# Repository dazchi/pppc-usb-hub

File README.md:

# Per-port Power Control USB HUB

## Key Features
* 3-port USB hub fully compatiable with USB High-Speed(480Hz), Full-Speed(12Hz) and Low-Speed(1.5MHz) devices
* Supports per-port power control, current limitation and thermal shutdown protection
* No special driver required, reuses the driver from the widely known CH340 USB-to-serial chip
* Supports 5V 2A external USB-C power supply
* Reverse current protection along with resetable fuse
* Relay: SRD-05VDC-SL-C 10A 30VDC, 10A 250VAC
* Customized settings stored in built-in flash memory

## Schematic & Layout (Designed w/ KiCAD 8.0)

## 3D Printed Case (Designed w/ Fusion 360)

## Basic Control Commands (Group Control)
Turn On:  ```A0 01 01 A2```
  
Turn Off: ```A0 01 00 A1```
  
*These commands are designed to mimic the command of **[USB RELAY](https://www.smart-prototyping.com/USB-Relay-1-Channel)** on purpose*  

## Advanced Control Commands

### Per-port control
Foramt: ```F0 {AA} {BB} {ZZ} ```  

* ```{AA}``` Port Address:  
  | Port | Address |
  |:----:|:-------:|
  | USB1 |   0x01  |
  | USB2 |   0x02  |
  | USB3 |   0x03  |
  | Relay|   0x04  |

*  ```{BB}``` On/Off:  
    * ON: ```0x01```  
    * OFF: ```0x00```  

* ```{ZZ}``` Checksum:  
 ```ZZ = (0xF0 + {AA} + {BB}) & 0xFF```

Example:  
* Turn on USB1: ```F0 01 01 F2```  
* Turn off Relay: ```F0 04 00 F4```  

### Write Device Settings
Format:  
* Command: ```AB CD EF 67 {X1 X2 X3 X4} ZZ```:

    *  ```{X1 X2 X3 X4}``` Device Settings:  
        |          |                       |
        |:--------:|:---------------------:|
        | ```X1``` |   USB1 Port Settings  |
        | ```X2``` |   USB2 Port Settings  |
        | ```X3``` |   USB3 Port Settings  |
        | ```X4``` |  Relay Port Settings  |
        ```c
        typedef struct DeviceSettings
        {
            PortSettings_t usb1;
            PortSettings_t usb2;
            PortSettings_t usb3;
            PortSettings_t relay;
        } __attribute__((packed)) DeviceSettings_t;
        ```
        * Port Settings:  
            |  Bit Field |  Setting  |  Description |
            |:--------:|:---------------------:|:------------------|
            | b0 |   Port Default State  | Default state of port while power on  |
            | b1 |   *Group Control       | 0: Disable group control (ignores **Basic Control Commands**)<br>1: Enable group control
            | b2 |   *Polarity  | Polarity of the port during group control<br>0: Default polarity<br>1: Reversed polarity
            | b3 ~ b7 |  Reserved  |  Reserved for future use   |

            **The **Group Control** and the **Polarity** only affets the **Basic Control Commands***
            ```c
            typedef struct PortSettings
            {
                uint8_t defaultState :1;
                uint8_t groupControl :1;
                uint8_t polarity :1;
                uint8_t reserved :5;
            } __attribute__((packed)) PortSettings_t;
            ```
    * ```{ZZ}``` Checksum:  
    ```ZZ = (0xAB + 0xCD + 0xEF + 0x67 + {X1} {X2} {X3} {X4}) & 0xFF```

* Response:  
    ```SUCCESS``` or ```FAILED```

Example:  
* Defaut Devcie Settings  
    TX: ```AB CD EF 67 07 07 07 02 E5```  
    RX: ```SUCCESS```  

    This command sets the default state of USB1, USB2 and USB3 to On, the default state of Relay to Off.  
    The "Turn on" command ```A0 01 01 A2``` turns on the relay but turns off USB1, USB2 and USB3.  
    The "Turn off" command ```A0 01 00 A1``` turns off the relay but turns on USB1, USB2 and USB3.

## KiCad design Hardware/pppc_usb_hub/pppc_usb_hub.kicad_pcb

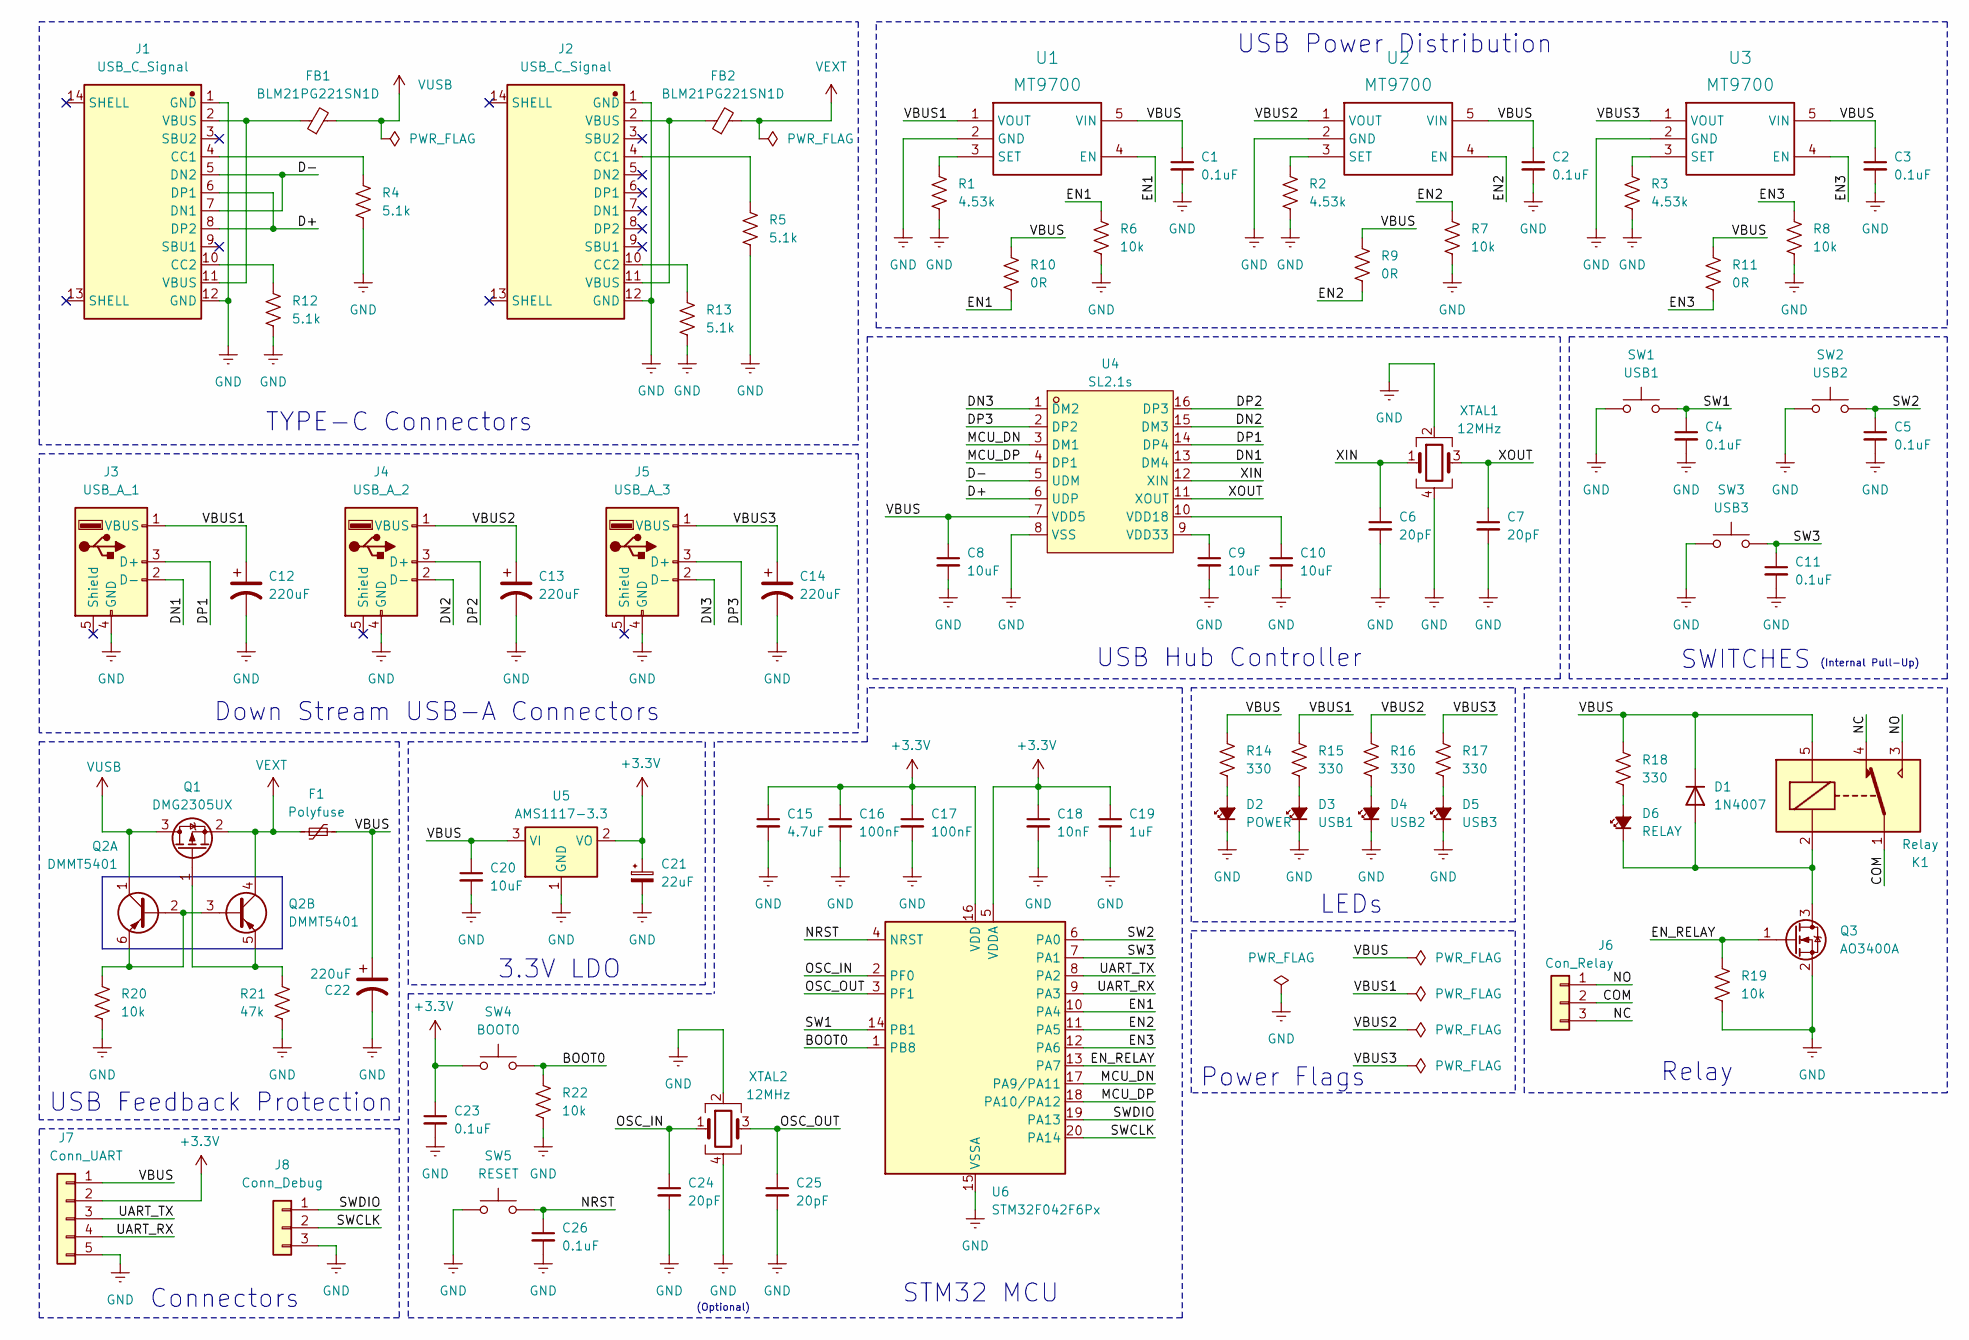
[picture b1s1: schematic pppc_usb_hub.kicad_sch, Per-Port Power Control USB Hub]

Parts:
C1, C2, C3, C4, C5, C11, C23, C26: 0.1uF; C_0603_1608Metric
C6, C7, C24, C25: 20pF; C_0603_1608Metric
C8, C9, C10, C20: 10uF; C_0603_1608Metric
C12, C13, C14, C22: 220uF; CP_Elec_6.3x7.7
C15: 4.7uF; C_0603_1608Metric
C16, C17: 100nF; C_0603_1608Metric
C18: 10nF; C_0603_1608Metric
C19: 1uF; C_0603_1608Metric
C21: 22uF; CP_EIA-3216-10_Kemet-I
D1: 1N4007; D_SOD-123F
D2: POWER; LED_0603_1608Metric
D3: USB1; LED_0603_1608Metric
D4: USB2; LED_0603_1608Metric
D5: USB3; LED_0603_1608Metric
D6: RELAY; LED_0603_1608Metric
F1: Polyfuse; C_0805_2012Metric
FB1, FB2: BLM21PG221SN1D; Fuse_0805_2012Metric
J1, J2: USB_C_Signal; USB-C-SMD_TYPE-C-6PIN-2MD-073
J3: USB_A_1; USB-A-TH_AF-10.0-HC6.3
J4: USB_A_2; USB-A-TH_USB-M-22
J5: USB_A_3; USB-A-TH_USB-M-22
J6: Con_Relay; CONN-TH_3P-P5.08_DB128L-5.08-3P-OG-S
J7: Conn_UART; PinHeader_1x05_P2.54mm_Vertical
J8: Conn_Debug; PinHeader_1x03_P2.54mm_Vertical
K1: Relay; Relay_SPDT_SANYOU_SRD_Series_Form_C
Q1: DMG2305UX; SOT-23
Q2: DMMT5401; SOT-23-6
Q3: AO3400A; SOT-23
R1, R2, R3: 4.53k; R_0603_1608Metric
R4, R5, R12, R13: 5.1k; R_0603_1608Metric
R6, R7, R8, R19, R20, R22: 10k; R_0603_1608Metric
R9, R10, R11: 0R; R_0603_1608Metric
R14, R15, R16, R17, R18: 330; R_0603_1608Metric
R21: 47k; R_0603_1608Metric
SW1: USB1; SW-SMD_GT-TC020B-H035-L05
SW2: USB2; SW-SMD_GT-TC020B-H035-L05
SW3: USB3; SW-SMD_GT-TC020B-H035-L05
SW4: BOOT0; SW-SMD_GT-TC020B-H035-L05
SW5: RESET; SW-SMD_L6.0-W3.3-LS8.0
U1, U2, U3: MT9700; SOT-23-5_L3.0-W1.7-P0.95-LS2.8-BR
U4: SL2.1s; SSOP-16_L4.6-W2.6-P0.53-LS4.0-BL
U5: AMS1117-3.3; SOT-223-3_TabPin2
U6: STM32F042F6Px; TSSOP-20_4.4x6.5mm_P0.65mm
XTAL1, XTAL2: 12MHz; OSC-SMD_4P-L3.2-W2.5-BL

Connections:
+3.3V: C15.1, C16.1, C17.1, C18.1, C19.1, C21.1, C23.1, J7.2, SW4.2, U5.2 (VO), U6.5 (VDDA), U6.16 (VDD)
/BOOT0: R22.1, SW4.1, U6.1 (PB8)
/COM: J6.2, K1.1
/D+: J1.6 (DP1), J1.8 (DP2), U4.6 (UDP)
/D-: J1.5 (DN2), J1.7 (DN1), U4.5 (UDM)
/DN1: J3.2 (D-), U4.13 (DM4)
/DN2: J4.2 (D-), U4.15 (DM3)
/DN3: J5.2 (D-), U4.1 (DM2)
/DP1: J3.3 (D+), U4.14 (DP4)
/DP2: J4.3 (D+), U4.16 (DP3)
/DP3: J5.3 (D+), U4.2 (DP2)
/EN1: R6.1, R10.2, U1.4 (EN), U6.10 (PA4)
/EN2: R7.1, R9.2, U2.4 (EN), U6.11 (PA5)
/EN3: R8.1, R11.2, U3.4 (EN), U6.12 (PA6)
/EN_RELAY: Q3.1 (G), R19.1, U6.13 (PA7)
/MCU_DN: U4.3 (DM1), U6.17 (PA9/PA11)
/MCU_DP: U4.4 (DP1), U6.18 (PA10/PA12)
/NC: J6.3, K1.4
/NO: J6.1, K1.3
/NRST: C26.1, SW5.1, U6.4 (NRST)
/OSC_IN: C24.1, U6.2 (PF0), XTAL2.1
/OSC_OUT: C25.1, U6.3 (PF1), XTAL2.3
/SW1: C4.1, SW1.1, U6.14 (PB1)
/SW2: C5.1, SW2.1, U6.6 (PA0)
/SW3: C11.1, SW3.1, U6.7 (PA1)
/SWCLK: J8.2, U6.20 (PA14)
/SWDIO: J8.1, U6.19 (PA13)
/UART_RX: J7.4, U6.9 (PA3)
/UART_TX: J7.3, U6.8 (PA2)
/VBUS: C1.1, C2.1, C3.1, C8.1, C20.1, C22.1, D1.1 (K), F1.2, J7.1, K1.5, R9.1, R10.1, R11.1, R14.1, R18.1, U1.5 (VIN), U2.5 (VIN), U3.5 (VIN), U4.7 (VDD5), U5.3 (VI)
/VBUS1: C12.1, J3.1 (VBUS), R15.1, U1.1 (VOUT)
/VBUS2: C13.1, J4.1 (VBUS), R16.1, U2.1 (VOUT)
/VBUS3: C14.1, J5.1 (VBUS), R17.1, U3.1 (VOUT)
/XIN: C6.1, U4.12 (XIN), XTAL1.1
/XOUT: C7.1, U4.11 (XOUT), XTAL1.3
GND: C1.2, C2.2, C3.2, C4.2, C5.2, C6.2, C7.2, C8.2, C9.2, C10.2, C11.2, C12.2, C13.2, C14.2, C15.2, C16.2, C17.2, C18.2, C19.2, C20.2, C21.2, C22.2, C23.2, C24.2, C25.2, C26.2, D2.1 (K), D3.1 (K), D4.1 (K), D5.1 (K), J1.1 (GND), J1.12 (GND), J2.1 (GND), J2.12 (GND), J3.4 (GND), J4.4 (GND), J5.4 (GND), J7.5, J8.3, Q3.2 (S), R1.2, R2.2, R3.2, R4.2, R5.2, R6.2, R7.2, R8.2, R12.2, R13.2, R19.2, R20.2, R21.2, R22.2, SW1.2, SW2.2, SW3.2, SW5.2, U1.2 (GND), U2.2 (GND), U3.2 (GND), U4.8 (VSS), U5.1 (GND), U6.15 (VSSA), XTAL1.2, XTAL1.4, XTAL2.2, XTAL2.4
unnamed: D1.2 (A), D6.1 (K), K1.2, Q3.3 (D)
unnamed: D2.2 (A), R14.2
unnamed: D3.2 (A), R15.2
unnamed: D4.2 (A), R16.2
unnamed: D5.2 (A), R17.2
unnamed: D6.2 (A), R18.2
unnamed: FB1.1, J1.2 (VBUS), J1.11 (VBUS)
unnamed: FB2.1, J2.2 (VBUS), J2.11 (VBUS)
unnamed: J1.4 (CC1), R4.1
unnamed: J1.10 (CC2), R12.1
unnamed: J2.4 (CC1), R5.1
unnamed: J2.10 (CC2), R13.1
unnamed: Q1.1 (G), Q2.5 (E2), R21.1
unnamed: Q2.2 (B1), Q2.3 (B2), Q2.6 (E1), R20.1
unnamed: R1.1, U1.3 (SET)
unnamed: R2.1, U2.3 (SET)
unnamed: R3.1, U3.3 (SET)
unnamed: C10.1, U4.10 (VDD18)
unnamed: C9.1, U4.9 (VDD33)
VEXT: F1.1, FB2.2, Q1.2 (S), Q2.4 (C2)
VUSB: FB1.2, Q1.3 (D), Q2.1 (C1)

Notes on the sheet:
3.3V LDO
Relay
Connectors
(Internal Pull-Up)
Power Flags
(Optional)
LEDs
TYPE-C Connectors
STM32 MCU
USB Hub Controller
Down Stream USB-A Connectors
USB Power Distribution
SWITCHES
USB Feedback Protection

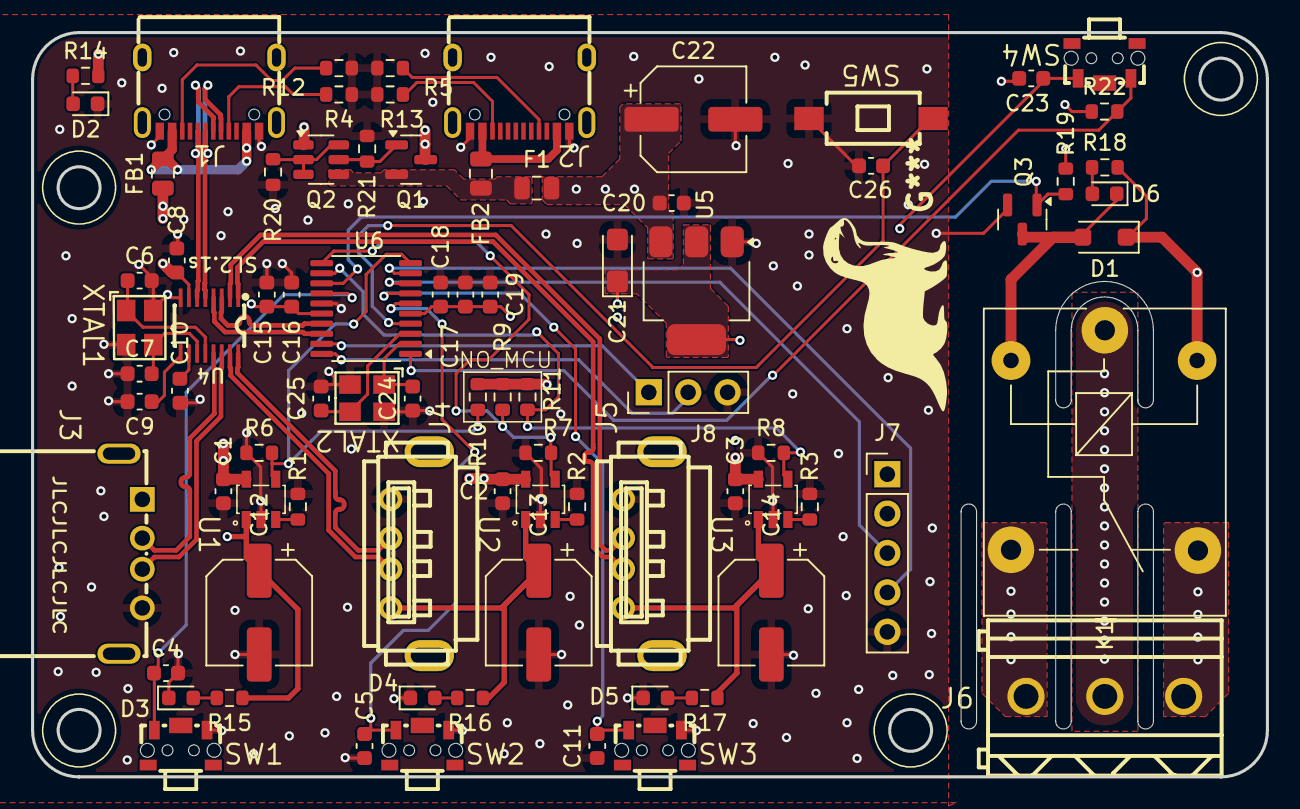
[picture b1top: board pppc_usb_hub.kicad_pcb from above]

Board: 4 copper layers, 79.6 x 48.0 mm, 82 parts (0 on the bottom side), 57 nets.

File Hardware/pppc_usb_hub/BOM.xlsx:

Reference | Value | Datasheet | Footprint | Qty | DNP | MSRP |  | Total
C1,C2,C3,C4,C5,C11,C25 | 0.1uF | https://www.lcsc.com/product-detail/Multilayer-Ceramic-Capac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 | Capacitor_SMD:C_0201_0603Metric | 7 |  | 2.3999999999999998E-3 |  | 3.8712
C6,C7,C23,C24 | 20pF | https://www.lcsc.com/product-detail/Multilayer-Ceramic-Capac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 | Capacitor_SMD:C_0201_0603Metric | 4 |  | 1.4E-2
C8,C9,C10,C20 | 10uF | https://www.lcsc.com/product-detail/Multilayer-Ceramic-Capac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 | Capacitor_SMD:C_0201_0603Metric | 4 |  | 4.4000000000000003E-3
C12,C13,C14,C22 | 220uF | https://www.lcsc.com/product-detail/Solid-Capacitors_Honor-E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 | Capacitor_SMD:CP_Elec_6.3x7.7 | 4 |  | 0.14080000000000001
C15 | 4.7uF | https://www.lcsc.com/product-detail/Multilayer-Ceramic-Capac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 | Capacitor_SMD:C_0201_0603Metric | 1 |  | 4.1000000000000003E-3
C16,C17 | 100nF | https://www.lcsc.com/product-detail/Multilayer-Ceramic-Capac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 | Capacitor_SMD:C_0201_0603Metric | 2 |  | 2.3999999999999998E-3
C18 | 10nF | https://www.lcsc.com/product-detail/Multilayer-Ceramic-Capac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 | Capacitor_SMD:C_0201_0603Metric | 1 |  | 1.9E-3
C19 | 1uF | https://www.lcsc.com/product-detail/Multilayer-Ceramic-Capac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 | Capacitor_SMD:C_0201_0603Metric | 1 |  | 4.1999999999999997E-3
C21 | 22uF | https://www.lcsc.com/product-detail/Tantalum-Capacitors_KEME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 | Capacitor_Tantalum_SMD:CP_EIA-3216-10_Kemet-I | 1 |  | 8.0100000000000005E-2
D1 | 1N4007 | https://www.lcsc.com/product-detail/Diodes-General-Purpose_M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 | Diode_SMD:D_SOD-123F | 1 |  | 3.8E-3
D2 | POWER | https://www.lcsc.com/product-detail/Light-Emitting-Diodes-LE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 | LED_SMD:LED_0201_0603Metric | 1 |  | 5.1000000000000004E-3
D3 | USB1 | https://www.lcsc.com/product-detail/Light-Emitting-Diodes-LE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 | LED_SMD:LED_0201_0603Metric | 1 |  | 5.3E-3
D4 | USB2 | https://www.lcsc.com/product-detail/Light-Emitting-Diodes-LE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 | LED_SMD:LED_0201_0603Metric | 1 |  | 5.3E-3
D5 | USB3 | https://www.lcsc.com/product-detail/Light-Emitting-Diodes-LE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 | LED_SMD:LED_0201_0603Metric | 1 |  | 5.3E-3
D6 | RELAY | https://www.lcsc.com/product-detail/Light-Emitting-Diodes-LE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 | LED_SMD:LED_0201_0603Metric | 1 |  | 5.3E-3
F1 | Polyfuse | https://www.lcsc.com/product-detail/Resettable-Fuses_LUTE-08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 | Capacitor_SMD:C_0805_2012Metric | 1 |  | 5.8400000000000001E-2
FB1,FB2 | BLM21PG221SN1D | https://www.lcsc.com/product-detail/Ferrite-Beads_Murata-Ele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 | Fuse:Fuse_0805_2012Metric | 2 |  | 1.4800000000000001E-2
J1,J2 | USB_C_Signal | https://www.lcsc.com/product-detail/USB-Connectors_SHOU-HAN-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 | PCBLIB_USB-C-SMD_TYPE-C-6PIN-2MD-073_2024-05-18:USB-C-SMD_TYPE-C-6PIN-2MD-073 | 2 |  | 5.0099999999999999E-2
J3 | USB_A_1 | https://www.lcsc.com/product-detail/USB-Connectors_SHOU-HAN-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 | PCBLIB_USB-A-TH_AF-10.0-HC6.3_2024-05-20:USB-A-TH_AF-10.0-HC6.3 | 1 |  | 3.6200000000000003E-2
J4 | USB_A_2 | https://www.lcsc.com/product-detail/USB-Connectors_Ckmtw-She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 | PCBLIB_USB-A-TH_USB-M-22_2024-05-19:USB-A-TH_USB-M-22 | 1 |  | 0.15040000000000001
J5 | USB_A_3 | https://www.lcsc.com/product-detail/USB-Connectors_Ckmtw-She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 | PCBLIB_USB-A-TH_USB-M-22_2024-05-19:USB-A-TH_USB-M-22 | 1 |  | 0.15040000000000001
J6 | Con_Relay | https://www.lcsc.com/product-detail/Screw-terminal_DORABO-DB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 | PCBLIB_CONN-TH_3P-P5.08_DB128L-5.08-3P-OG-S_2024-05-19:CONN-TH_3P-P5.08_DB128L-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 | 1 |  | 0.18010000000000001
J7 | Conn_UART | https://www.lcsc.com/product-detail/Pin-Headers_Hanbo-Electr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 | Connector_PinHeader_2.54mm:PinHeader_1x05_P2.54mm_Vertical | 1 |  | 2.23E-2
J8 | Conn_Debug | ~ | Connector_PinHeader_2.54mm:PinHeader_1x03_P2.54mm_Vertical | 1
K1 | Relay | https://www.lcsc.com/product-detail/Power-Relays_Ningbo-Song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 | Relay_THT:Relay_SPDT_SANYOU_SRD_Series_Form_C | 1 |  | 0.31240000000000001
Q1 | DMG2305UX | https://www.lcsc.com/product-detail/MOSFETs_TECH-PUBLIC-DMG2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 | Package_TO_SOT_SMD:SOT-23 | 1 |  | 5.1700000000000003E-2
Q2 | DMMT5401 | https://www.lcsc.com/product-detail/Bipolar-Transistors-BJT_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 | Package_TO_SOT_SMD:SOT-23-6 | 1 |  | 0.16830000000000001
Q3 | AO3400A | https://www.lcsc.com/product-detail/MOSFETs_UMW-Youtai-Semic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 | Package_TO_SOT_SMD:SOT-23 | 1 |  | 2.7799999999999998E-2
R1,R2,R3 | 4.53k | https://www.lcsc.com/product-detail/Chip-Resistor-Surface-Mo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 | Resistor_SMD:R_0201_0603Metric | 3 |  | 1.1999999999999999E-3
R4,R5,R12,R13 | 5.1k | https://www.lcsc.com/product-detail/Chip-Resistor-Surface-Mo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 | Resistor_SMD:R_0201_0603Metric | 4 |  | 0.0010
R6,R7,R8,R19,R20,R22 | 10k | https://www.lcsc.com/product-detail/Chip-Resistor-Surface-Mo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 | Resistor_SMD:R_0201_0603Metric | 6 |  | 8.9999999999999998E-4
R9,R10,R11 | 0R | ~ | Resistor_SMD:R_0201_0603Metric | 3
R14,R15,R16,R17,R18 | 330 | https://www.lcsc.com/product-detail/Chip-Resistor-Surface-Mo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 | Resistor_SMD:R_0201_0603Metric | 5 |  | 1E-3
R21 | 47k | https://www.lcsc.com/product-detail/Chip-Resistor-Surface-Mo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 | Resistor_SMD:R_0201_0603Metric | 1 |  | 1E-3
SW1 | USB1 | https://www.lcsc.com/product-detail/Tactile-Switches_G-Switc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 | PCBLIB_SW-SMD_GT-TC020B-H035-L05_2024-05-21:SW-SMD_GT-TC020B-H035-L05 | 1 |  | 7.2599999999999998E-2
SW2 | USB2 | https://www.lcsc.com/product-detail/Tactile-Switches_G-Switc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 | PCBLIB_SW-SMD_GT-TC020B-H035-L05_2024-05-21:SW-SMD_GT-TC020B-H035-L05 | 1 |  | 7.2599999999999998E-2
SW3 | USB3 | https://www.lcsc.com/product-detail/Tactile-Switches_G-Switc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 | PCBLIB_SW-SMD_GT-TC020B-H035-L05_2024-05-21:SW-SMD_GT-TC020B-H035-L05 | 1 |  | 7.2599999999999998E-2
SW4 | BOOT0 | https://www.lcsc.com/product-detail/Tactile-Switches_XKB-Con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 | PCBLIB_SW-SMD_L6.0-W3.3-LS8.0_2024-05-19:SW-SMD_L6.0-W3.3-LS8.0 | 1 |  | 0.0323
SW5 | RESET | https://www.lcsc.com/product-detail/Tactile-Switches_XKB-Con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 | PCBLIB_SW-SMD_L6.0-W3.3-LS8.0_2024-05-19:SW-SMD_L6.0-W3.3-LS8.0 | 1 |  | 0.0323
U1,U2,U3 | MT9700 | https://www.lcsc.com/product-detail/span-style-background-co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 | PCBLIB_SOT-23-5_L3.0-W1.7-P0.95-LS2.8-BR_2024-05-18:SOT-23-5_L3.0-W1.7-P0.95-LS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 | 3 |  | 3.56E-2
U4 | SL2.1s | https://www.lcsc.com/product-detail/USB-Converters_CoreChips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 | PCB_NEW_PCB_2024-05-14:SSOP-16_L4.6-W2.6-P0.53-LS4.0-BL | 1 |  | 0.20499999999999999
U5 | AMS1117-3.3 | https://www.lcsc.com/product-detail/Linear-Voltage-Regulator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 | Package_TO_SOT_SMD:SOT-223-3_TabPin2 | 1 |  | 0.1298
U6 | STM32F042F6Px | https://www.lcsc.com/product-detail/Microcontroller-Units-MC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 | Package_SO:TSSOP-20_4.4x6.5mm_P0.65mm | 1 |  | 1.1457999999999999
XTAL1,XTAL2 | 12MHz | https://www.lcsc.com/product-detail/Crystals_YXC-X322512MSB4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 | PCBLIB_OSC-SMD_4P-L3.2-W2.5-BL_2024-05-18:OSC-SMD_4P-L3.2-W2.5-BL | 2 |  | 5.7099999999999998E-2

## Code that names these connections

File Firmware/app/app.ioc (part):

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Mcu.Name=STM32F042F6Px
Mcu.Package=TSSOP20
Mcu.UserName=STM32F042F6Px
PA0.Signal=GPIO_Input
PA1.Signal=GPIO_Input
PA11.Mode=Device
PA11.Signal=USB_DM
PA12.Mode=Device
PA12.Signal=USB_DP
PA13.Mode=Serial_Wire
PA13.Signal=SYS_SWDIO
PA14.Mode=Serial_Wire
PA14.Signal=SYS_SWCLK
PA2.Mode=Asynchronous
PA2.Signal=USART2_TX
PA3.Mode=Asynchronous
PA3.Signal=USART2_RX
PA4.Signal=GPIO_Output
PA5.Signal=GPIO_Output
PA6.Signal=GPIO_Output
PA7.Signal=GPIO_Output
PB1.Signal=GPIO_Input
PB8.Signal=GPIO_Input
RCC.SYSCLKFreq_VALUE=48000000
RCC.SYSCLKSource=RCC_SYSCLKSOURCE_HSI48
board=custom

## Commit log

2024-07-01 Add README.md and delete unnecessary files
2024-07-03 Add device settings and enable DMA IRQ
2024-07-05 Store settings in Flash
2024-07-11 Add more infomations in README and fix polarity settings
